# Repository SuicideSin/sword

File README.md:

Simple 3d printable sword with a lighted blade.

WIP

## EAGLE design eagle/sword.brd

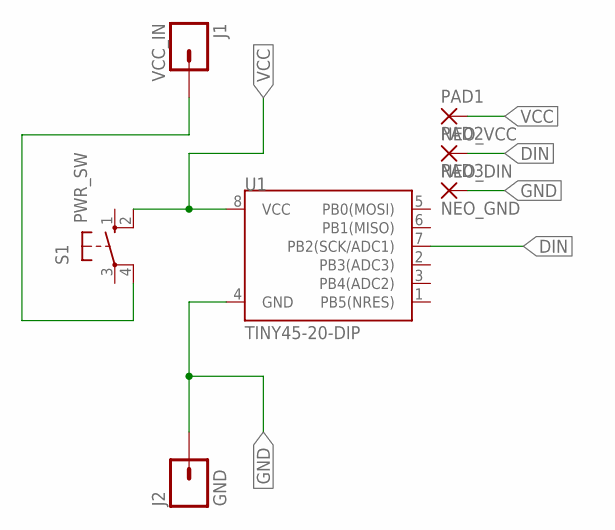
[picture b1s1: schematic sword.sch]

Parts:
J1: VCC_IN; 1X01_LONGPAD
J2: GND; 1X01_LONGPAD
PAD1: NEO_VCC; SMD1,27-2,54
PAD2: NEO_DIN; SMD1,27-2,54
PAD3: NEO_GND; SMD1,27-2,54
S1: PWR_SW; B3F-10XX
U1: TINY45-20-DIP; DIP08

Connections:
DIN: PAD2.1, U1.7 (PB2(SCK/ADC1))
GND: J2.1, PAD3.1, U1.4 (GND)
VCC: PAD1.1, S1.2 (S1), U1.8 (VCC)
VCC_SW: J1.1, S1.4 (P1)

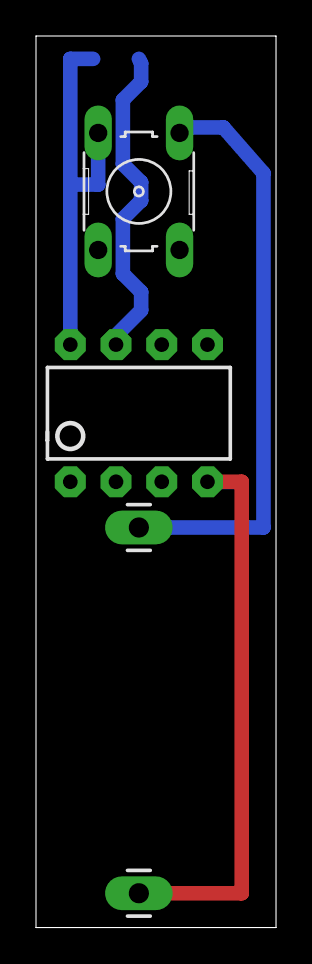
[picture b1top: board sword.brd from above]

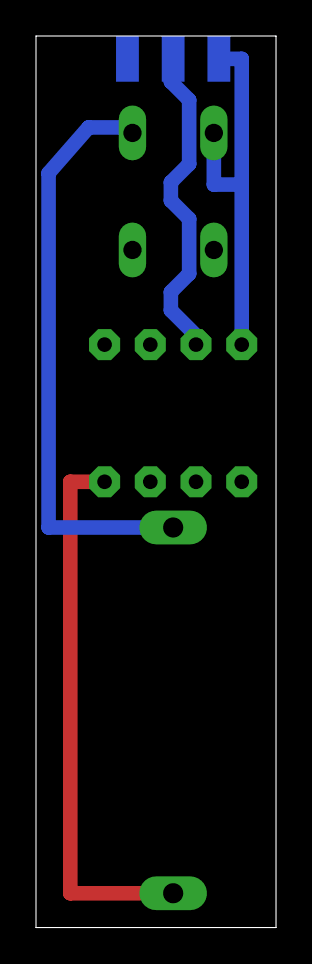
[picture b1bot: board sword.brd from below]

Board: 2 copper layers, 13.3 x 49.5 mm, 7 parts (3 on the bottom side), 4 nets.

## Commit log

2017-01-19 made everything centered across y axis.
2017-01-19 smaller blade
2017-01-20 redesigned for hopefully easy printing
2017-01-20 new stls
2017-01-21 added board an rearranged files
2017-01-21 readme
2017-01-21 image
2017-01-21 major schematic fail...
2017-01-21 fixed button spacing
2017-01-21 added battery "connector"
2017-01-21 shrunk just a little
2017-01-21 new button height
2017-01-21 images
2017-01-21 image rotate
2017-01-21 you ROTATE picture
2017-02-02 changed board to use a standard cr2032 socket
2017-02-02 added gerber files
2017-02-10 complete redesign of board (super skinny so that price is cheap)
2017-03-30 swapped battery around
2017-04-01 made button less thick

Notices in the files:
parts and their libraries:
SparkFun-Connectors: Licensing: Creative Commons ShareAlike 4.0 International - https://creativecommons.org/licenses/by-sa/4.0
